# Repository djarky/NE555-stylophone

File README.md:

# NE555-stylophone
PCB board made in Eagle

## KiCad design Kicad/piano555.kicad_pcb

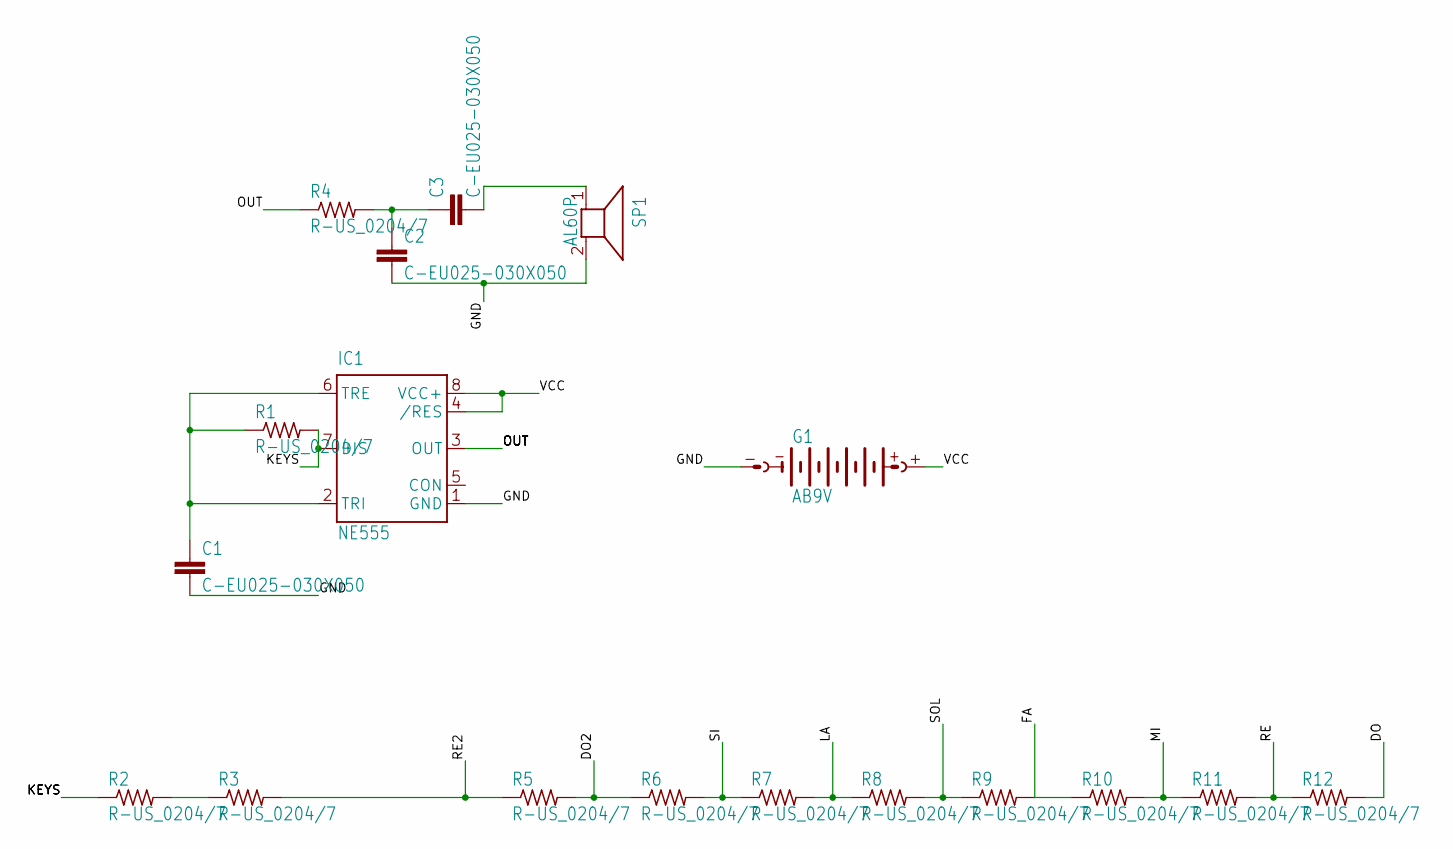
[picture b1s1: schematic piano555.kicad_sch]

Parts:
C1, C2, C3: C-EU025-030X050; C025-030X050
G1: AB9V
IC1: NE555; DIL-08
R1, R2, R3, R4, R5, R6, R7, R8, R9, R10, R11, R12: R-US_0204/7; 0204_7
SP1: AL60P

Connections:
DO: R12.2
DO2: R5.2, R6.1
FA: R9.2, R10.1
GND: C1.2, C2.2, G1.-, IC1.1 (GND), SP1.2
KEYS: IC1.7 (DIS), R1.2, R2.1
LA: R7.2, R8.1
MI: R10.2, R11.1
unnamed: C1.1, IC1.2 (TRI), IC1.6 (TRE), R1.1
unnamed: R2.2, R3.1
unnamed: C2.1, C3.1, R4.2
unnamed: C3.2, SP1.1
OUT: IC1.3 (OUT), R4.1
RE: R11.2, R12.1
RE2: R3.2, R5.1
SI: R6.2, R7.1
SOL: R8.2, R9.1
VCC: G1.+, IC1.4 (/RES), IC1.8 (VCC+)

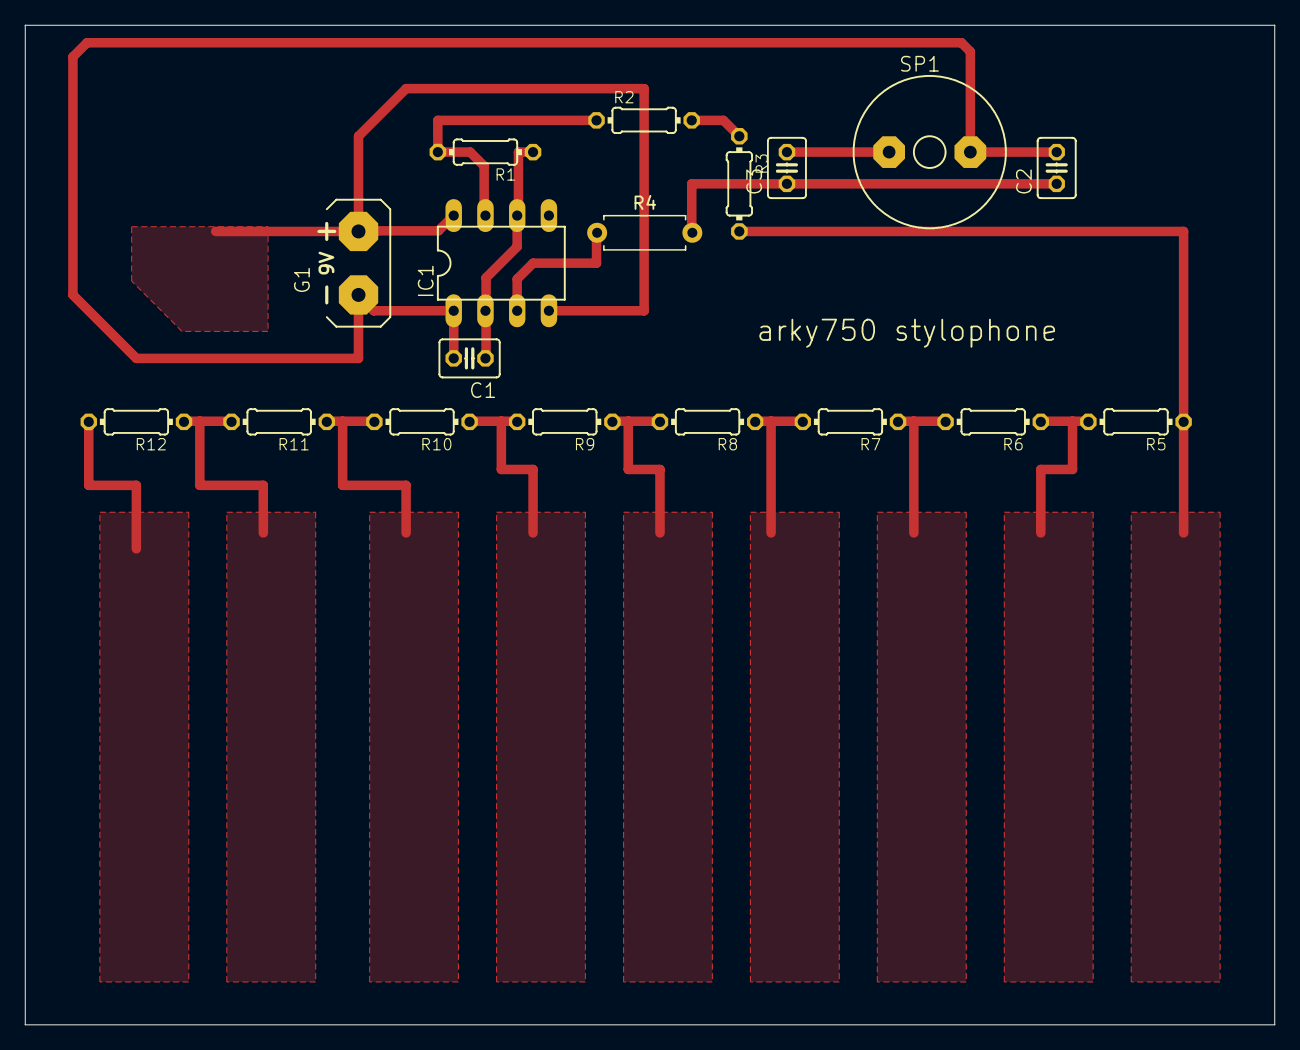
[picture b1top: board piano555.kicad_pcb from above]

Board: 2 copper layers, 100.0 x 80.0 mm, 18 parts (0 on the bottom side), 16 nets.

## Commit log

2025-05-20 Add files via upload
    TDA2003
2025-06-30 Rename render4.png to Kicad/render4.png
2025-06-30 Rename render3.png to blender/render3.png
2025-07-01 Rename testRender_0001.png to render5.png
